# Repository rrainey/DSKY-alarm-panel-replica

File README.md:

# DSKY Alarm Indicator Panel Replica

## The current PCB layout has passed testing.

This is a scale functional replica of the Alarm Indicator panel for the Apollo Guidance Computer. It is
designed to be part of a larger replica of the Display and Keyboard (DSKY) module of the AGC.

This project is composed of these component subfolders:

* artwork - artwork to be silk-screened onto the front transparent acrylic cover

* pcb - KiCad project for the controller PCB design

* firmware - circuitpython board definition and python-based test and controller firmware

* hardware - 3D-printable frame components designed using Fusion 360. STEP and Fusion source files available. Hardware models used in thie replica were derived from models found in the [AGC Mechanical CAD project](https://github.com/rrainey/agc-mechanical-cad).

## Exploded View of the Assembly

[This video](https://vimeo.com/393337269) will give you a sense of the internal construction of the unit. The panel
is a combinaton of white and yellow indicators. Like the original, incendescent lamps are used for each alarm
indicator. Yellow bezel inserts supply the indictor color where needed. An AT SAMD21 microcontroller drives the lamp from a 5V DC power
source. This microcontroller includes an I2C interface designed to be the source for external control of the unit.
There's also a USB interface, however, that's more for programming than operational use.

At the top is a clear acrylic plate (0.060" thick). On that, I silkscreen lamp labels and the frame outline. Below that, there are 14 translucent covers, one for each indicator lamp array. Each indicator is composed of three incandescent lamps. Yellow bezels are inserted where needed. The bezels and the translucent covers snap into the main body of the component.  

A lamp and microcontroller PCB slides into a recess under the main body.  This PCB is held in place by a frame. The frame is secured with screws. The main body and PCB frame are both designed to be 3D printed from Nylon, ABS, or PLA.

## Painting

The original NASA drawings for all variants of this component, [1006387D for example,](https://archive.org/stream/apertureCardBox439Part2NARASW_images#page/n409/mode/1up) point to [this NASA paint specification [1008809-1]](https://archive.org/stream/apertureCardBox443NARASW_images#page/n504/mode/1up). It states [FED-STD 36231](http://federalstandard595.com/36231/) as the external color of the unit.  Good quality historial photos (examples [here](https://www.icollector.com/Apollo-CM-DSKY_i21861898) and [here](http://nassp.sourceforge.net/wiki/File:DSKY.jpg)) seem to imply a slightly different shade of gray, though. 

I haven't decided how to reconcile this difference yet. I may custom mix using Nazdar pigments, or I might simply use [an aircraft-grade epoxy premix](https://www.skygeek.com/deft-01-series-epoxy-topcoat-gray-36231-mil-prf-227750g.html) of FS36231.

## Credits and Related Projects

This project is inspired by work by Ben Krasnow creating a DSKY Electroluminescent Panel replica. You'll
find information about that project in [this Applied Science video](https://www.youtube.com/watch?v=Z2o_Sp2-aBo) by Ben. Like Ben's E/L display, this project is driven by an AT SAMD21 microcontroller chip; the same chip is used in the multiple Adafruit microcontroller boards, including the Adafruit Trinket M0.

## DSKY Alarm Indicator Replica License

Creative Commons Attribution/Share-Alike, all text above must be included in any redistribution. See license.txt for additional details.

## Adafruit Trinket M0 License

This project includes hardware design elements from the Adafruit [Trinket M0 PCB project](https://github.com/adafruit/Adafruit-Trinket-M0-PCB). Adafruit invests time and resources providing this open source design, please support Adafruit and open-source hardware by purchasing products from [Adafruit](https://www.adafruit.com)!

The Trinket M0 was designed by Limor Fried/Ladyada for Adafruit Industries.

Creative Commons Attribution/Share-Alike, all text above must be included in any redistribution. See license.txt for additional details.

## My Background

My name is Riley Rainey. I'm a software developer by profession. I spent a number of years building aerospace simulations as my day job.

## Getting Support

There's no official support available, but you can [leave comments or create an issue](https://github.com/rrainey/DSKY-alarm-panel-replica/issues) in this GitHub project.

This work is licensed under a [Creative Commons Attribution-ShareAlike 4.0 International License](http://creativecommons.org/licenses/by-sa/4.0/).

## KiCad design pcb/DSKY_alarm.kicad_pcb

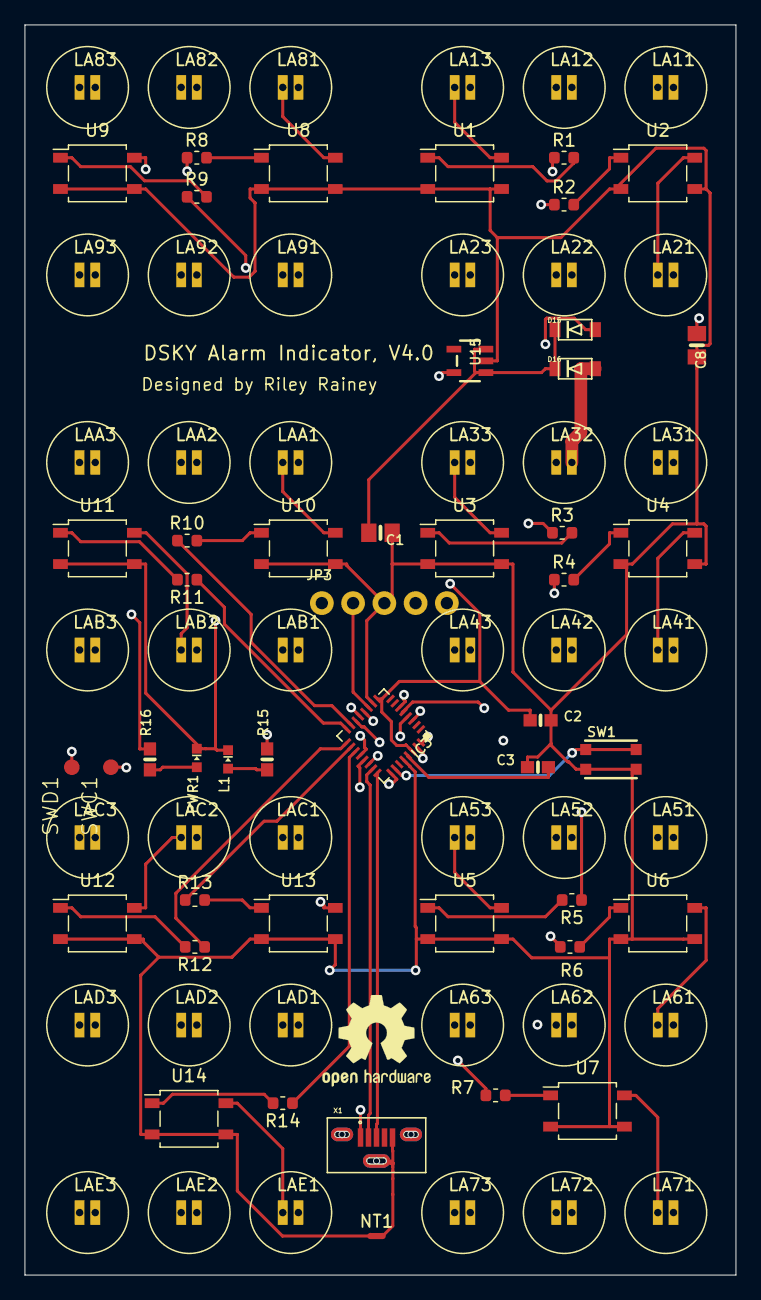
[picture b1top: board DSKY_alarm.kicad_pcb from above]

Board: 4 copper layers, 57.8 x 101.6 mm, 88 parts (0 on the bottom side), 58 nets.

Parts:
C1, C8: 10uF; 0805-NO
C2, C3: 1uF; 0603-NO
D15, D16: SCHOTTKY; SOD-123FL
IC3: ATSAMD21E; QFN32_5MM
JP3: HEADER-1X576MIL; 1X05_ROUND_76
L1: red; CHIPLED_0603_NOOUTLINE
LA11, LA12, LA13, LA21, LA22, LA23, LA31, LA32, LA33, LA41, LA42, LA43, LA51, LA52, LA53, LA61, LA62, LA63, LA71, LA72, LA73, LA81, LA82, LA83, LA91, LA92, LA93: Lamp; VCC7265
LAA1, LAA2, LAA3: Lamp; VCC7265
LAB1, LAB2, LAB3: Lamp; VCC7265
LAC1, LAC2, LAC3: Lamp; VCC7265
LAD1, LAD2, LAD3: Lamp; VCC7265
LAE1, LAE2, LAE3: Lamp; VCC7265
NT1: Net-Tie_2; NetTie-2_SMD_Pad0.5mm
PWR1: green; CHIPLED_0603_NOOUTLINE
R1, R2, R3, R4, R5, R6, R7, R8, R9, R10, R11, R12, R13, R14: 1.1K; R_0603_1608Metric
R15: 1.5K; 0603-NO
R16: 10K; 0603-NO
SW1: reset; BTN_KMR2_4.6X2.8
SWC1: TPB1,27; B1,27
SWD1: TPB1,27; B1,27
U1, U2, U3, U4, U5, U6, U7, U8, U9, U10, U11, U12, U13, U14: AQY232SZ; SO-4_4.4x4.3mm_P2.54mm
U15: AP2112K-3.3; SOT23-5
X1: Molex 105133 USB; MOLEX_105133-0001

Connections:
3.3V: C2.1, C8.1, IC3.9, IC3.30, R16.2, U15.5
/D0_A4_PA08_SDA: IC3.11, JP3.2
/D2_A1_PA09_SCL_MISO: IC3.12, JP3.4
/D+: IC3.24, X1.3
/D-: IC3.23, X1.2
/VOUT: C1.1, D15.C, D16.C, U15.1, U15.3
/~RESET: IC3.26, SW1.A, SW1.A'
GND: C1.2, C2.2, C3.2, C8.2, IC3.10, IC3.28, JP3.3, L1.C, NT1.1, NT1.2, PWR1.C, SW1.B, SW1.B', U1.2, U1.3, U2.2, U2.3, U3.2, U3.3, U4.2, U4.3, U5.2, U5.3, U6.2, U6.3, U7.2, U7.3, U8.2, U8.3, U9.2, U9.3, U10.2, U10.3, U11.2, U11.3, U12.2, U12.3, U13.2, U13.3, U14.2, U14.3, U15.2, X1.5, X1.S3
LA1_PA02: IC3.3, R1.1
LA2_PA03: IC3.4, R2.1
LA3_PA04: IC3.5, R3.1
LA4_P05: IC3.6, R4.1
LA5_PA19: IC3.20, R5.1
LA6_PA22: IC3.21, R6.1
LA7_PA23: IC3.22, R7.1
LA8_PA27: IC3.25, R8.1
LA9_PA11: IC3.14, R9.1
LA10_PA14: IC3.15, R10.1
LA11_PA15: IC3.16, R11.1
LA12_PA16: IC3.17, R12.1
LA13_PA17: IC3.18, R13.1
LA14_PA18: IC3.19, R14.1
unnamed: C3.1, IC3.29
unnamed: IC3.13, R15.2
unnamed: IC3.31, SWC1.TP
unnamed: IC3.32, SWD1.TP
unnamed: L1.A, R15.1
unnamed: LA11.1, LA12.1, LA13.1, U1.4
unnamed: LA21.1, LA22.1, LA23.1, U2.4
unnamed: LA31.1, LA32.1, LA33.1, U3.4
unnamed: LA41.1, LA42.1, LA43.1, U4.4
unnamed: LA51.1, LA52.1, LA53.1, U5.4
unnamed: LA61.1, LA62.1, LA63.1, U6.4
unnamed: LA71.1, LA72.1, LA73.1, U7.4
unnamed: LA81.1, LA82.1, LA83.1, U8.4
unnamed: LA91.1, LA92.1, LA93.1, U9.4
unnamed: LAA1.1, LAA2.1, LAA3.1, U10.4
unnamed: LAB1.1, LAB2.1, LAB3.1, U11.4
unnamed: LAC1.1, LAC2.1, LAC3.1, U12.4
unnamed: LAD1.1, LAD2.1, LAD3.1, U13.4
unnamed: LAE1.1, LAE2.1, LAE3.1, U14.4
unnamed: PWR1.A, R16.1
unnamed: R1.2, U1.1
unnamed: R2.2, U2.1
unnamed: R3.2, U3.1
unnamed: R4.2, U4.1
unnamed: R5.2, U5.1
unnamed: R6.2, U6.1
unnamed: R7.2, U7.1
unnamed: R8.2, U8.1
unnamed: R9.2, U9.1
unnamed: R10.2, U10.1
unnamed: R11.2, U11.1
unnamed: R12.2, U12.1
unnamed: R13.2, U13.1
unnamed: R14.2, U14.1
VBAT: D16.A, JP3.1, LA11.2, LA12.2, LA13.2, LA21.2, LA22.2, LA23.2, LA31.2, LA32.2, LA33.2, LA41.2, LA42.2, LA43.2, LA51.2, LA52.2, LA53.2, LA61.2, LA62.2, LA63.2, LA71.2, LA72.2, LA73.2, LA81.2, LA82.2, LA83.2, LA91.2, LA92.2, LA93.2, LAA1.2, LAA2.2, LAA3.2, LAB1.2, LAB2.2, LAB3.2, LAC1.2, LAC2.2, LAC3.2, LAD1.2, LAD2.2, LAD3.2, LAE1.2, LAE2.2, LAE3.2
VBUS: D15.A, X1.1

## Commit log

2020-02-15 Import artwork
2020-02-25 Fleshed-out project tree
2020-02-25 Moved README
2020-02-25 README and license updates
2020-02-27 Add exploded diagram/video
2020-03-11 Documentation updates
2020-04-05 Version 4 of the board
2020-04-05 Updated silscreen masters for EL display
2020-04-05 Revert "Updated silscreen masters for EL display"
    This reverts commit 9e19113deeaeeb9777c874106435cc4dff88d63f.
2020-04-05 Revert "Revert "Updated silscreen masters for EL display""
    This reverts commit fc3ec197f19d40117204c988a76f6fc0e565e775.
2020-04-05 add starter firmware and circuitpython board definition
2020-04-05 add git project attributes
2020-06-29 Add initial glass-to-PCB epoxy mask
2020-07-09 Updated V4 board to a two layer design
2020-07-09 Update version info and schematic PDF
2020-07-09 Cleanup of schematic files
2020-08-23 add initial test driver
2020-08-29 functional driver
2020-09-26 Change top-level status
2020-11-08 CC-BY-SA license

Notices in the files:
README.md:
CC BY-SA 4.0
